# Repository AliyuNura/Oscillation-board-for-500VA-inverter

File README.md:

# Oscillation-board-for-500VA-inverter
This is an oscillation board designed using SG3524 oscillator and an IRF3205 PWM

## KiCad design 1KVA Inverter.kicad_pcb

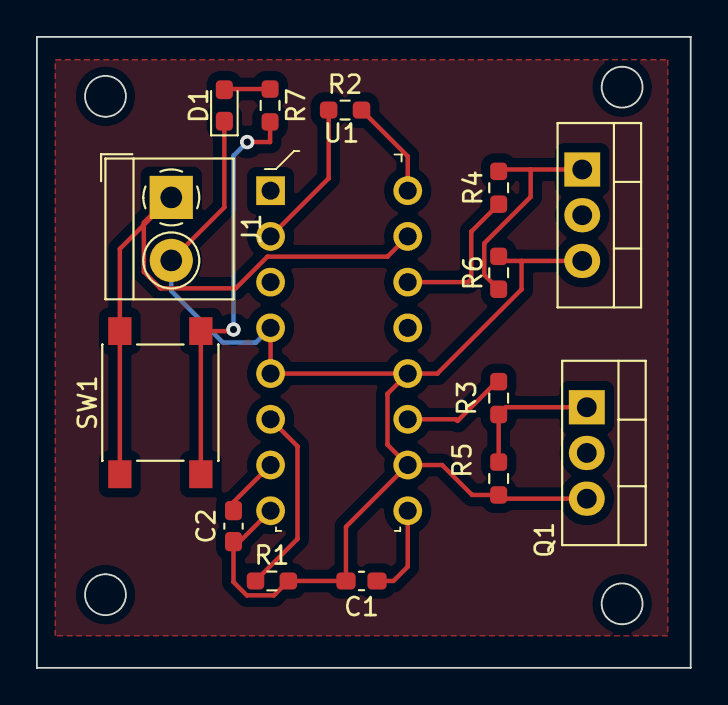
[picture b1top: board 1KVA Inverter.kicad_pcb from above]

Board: 2 copper layers, 36.3 x 35.1 mm, 15 parts (0 on the bottom side), 13 nets.

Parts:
C1: 10uF; C_0603_1608Metric_Pad1.08x0.95mm_HandSolder
C2: 56nF; C_0603_1608Metric_Pad1.08x0.95mm_HandSolder
D1: LED; LED_0603_1608Metric_Pad1.05x0.95mm_HandSolder
J1: Conn_01x02_Male; TerminalBlock_4Ucon_1x02_P3.50mm_Horizontal
Q1, Q2: IRF3205; TO-220-3_Vertical
R1: 470K; R_0603_1608Metric_Pad0.98x0.95mm_HandSolder
R2: 10k; R_0603_1608Metric_Pad0.98x0.95mm_HandSolder
R3, R4: 1K; R_0603_1608Metric_Pad0.98x0.95mm_HandSolder
R5, R6: 22K; R_0603_1608Metric_Pad0.98x0.95mm_HandSolder
R7: 1k; R_0603_1608Metric_Pad0.98x0.95mm_HandSolder
SW1: SW_Push; SW_Push_1P1T_NO_6x6mm_H9.5mm
U1: SG3525AN; DIP-16_W7.62mm

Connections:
GND: C1.2, C2.2, D1.1 (K), J1.2, Q1.3 (S), Q2.3 (S), R1.2, R5.2, R6.2, U1.4 (OSC_OUT), U1.5 (CT), U1.8 (SOFT_ST), U1.10 (SHUTDOWN), U1.12 (GND)
unnamed: D1.2 (A), R7.1
unnamed: J1.1, SW1.1, U1.15 (+V1)
unnamed: Q1.1 (G), R3.2, R5.1
unnamed: Q2.1 (G), R4.2, R6.1
unnamed: R7.2, SW1.2
unnamed: C1.1, U1.9 (COMP)
unnamed: C2.1, U1.7 (DIS)
unnamed: R2.1, U1.2 (N_I_IN)
unnamed: R3.1, U1.11 (OUT_A)
unnamed: R4.1, U1.14 (OUT_B)
unnamed: R1.1, U1.6 (RT)
unnamed: R2.2, U1.16 (VREF)

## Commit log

2022-09-13 adding files folder
2022-09-13 circuit diagram
